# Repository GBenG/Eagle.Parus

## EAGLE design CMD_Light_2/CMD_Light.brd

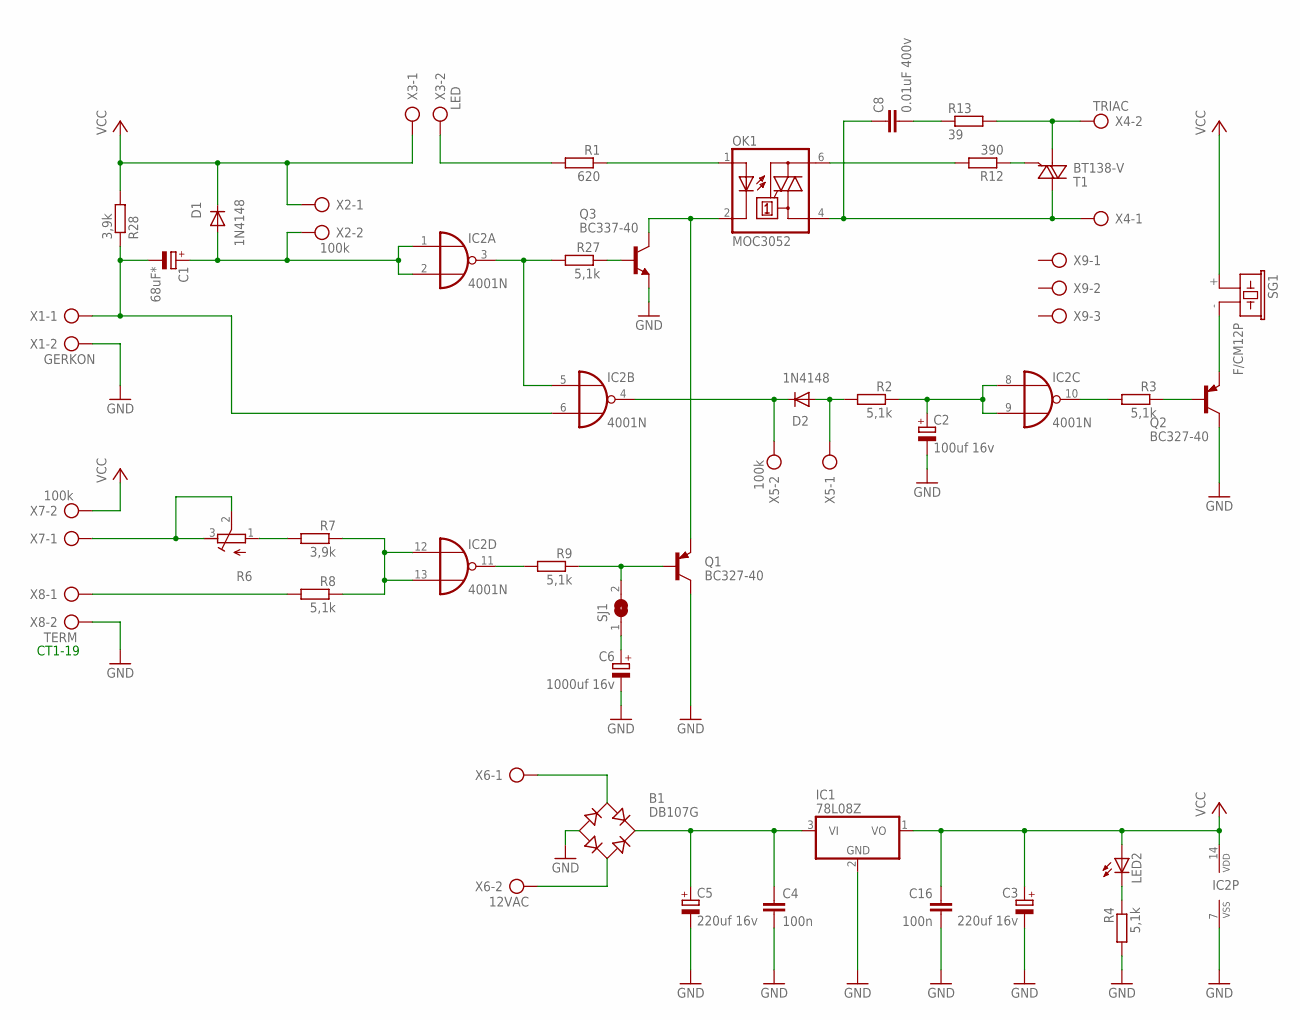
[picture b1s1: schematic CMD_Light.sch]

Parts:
B1: DB107G; DB
C1: 68uF*; E3,5-8
C2: 100uf 16v; E3,5-8
C3, C5: 220uf 16v; E3,5-8
C4, C16: 100n; C050-035X075
C6: 1000uf 16v; E5-10,5
C8: 0.01uF 400v; C075-063X106
D1: 1N4148; DO41-8
D2: 1N4148; DO41-10
IC1: 78L08Z; TO92
IC2: 4001N; DIL14
LED2: LED3MM
OK1: MOC3052; DIL06
Q1, Q2: BC327-40; TO92-EBC
Q3: BC337-40; TO92-EBC
R1: 620; 0207/10
R2, R3, R4, R8, R9, R27: 5,1k; 0207/10
R6: R-TRIMM3339P; RTRIM3339P
R7: 3,9k; 0207/10
R12: 390; 0207/10
R13: 39; 0411/12
R28: 3,9k; 0207/12
SG1: F/CM12P
SJ1: SJ
T1: BT138-V; TO220BV
X1: GERKON; AK500/2
X2, X5, X7: 100k; AK500/2
X3: LED; AK500/2
X4: TRIAC; AK500/2
X6: 12VAC; AK500/2
X8: TERM; AK500/2
X9: AK500/3

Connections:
GND: B1.-, C2.-, C3.-, C4.2, C5.-, C6.-, C16.2, IC1.2 (GND), IC2.7 (VSS), Q1.C, Q2.C, Q3.E, R4.2, X1.2, X8.2
unnamed: Q3.B, R27.1
unnamed: IC2.3 (O), IC2.5 (I0), R27.2
unnamed: C1.-, IC2.6 (I1), R28.1, X1.1
unnamed: OK1.1 (A), R1.1
unnamed: OK1.2 (C), Q1.E, Q3.C
unnamed: C6.+, SJ1.1
unnamed: R12.1, T1.G
unnamed: R1.2, X3.2
unnamed: B1.AC2, X6.2
unnamed: C2.+, IC2.8 (I0), IC2.9 (I1), R2.1
unnamed: IC2.10 (O), R3.2
unnamed: Q2.B, R3.1
unnamed: R13.2, T1.T1 (A1), X4.2
unnamed: Q2.E, SG1.- (2)
unnamed: B1.+, C4.1, C5.+, IC1.3 (VI)
unnamed: D2.A, R2.2, X5.1
unnamed: C8.2, R13.1
unnamed: C1.+, D1.A, IC2.1 (I0), IC2.2 (I1), X2.2
unnamed: IC2.12 (I0), IC2.13 (I1), R7.1, R8.1
unnamed: LED2.K (C), R4.1
unnamed: R6.2 (S), R6.3 (E), X7.1
unnamed: IC2.11 (O), R9.2
unnamed: R6.1 (A), R7.2
unnamed: R8.2, X8.1
unnamed: D2.C, IC2.4 (O), X5.2
unnamed: B1.AC1, X6.1
unnamed: OK1.6 (A2), R12.2
unnamed: Q1.B, R9.1, SJ1.2
unnamed: C8.1, OK1.4 (A1), T1.T2 (A2), X4.1
VCC: C3.+, C16.1, D1.C, IC1.1 (VO), IC2.14 (VDD), LED2.A, R28.2, SG1.+ (1), X2.1, X3.1, X7.2

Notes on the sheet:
CT1-19

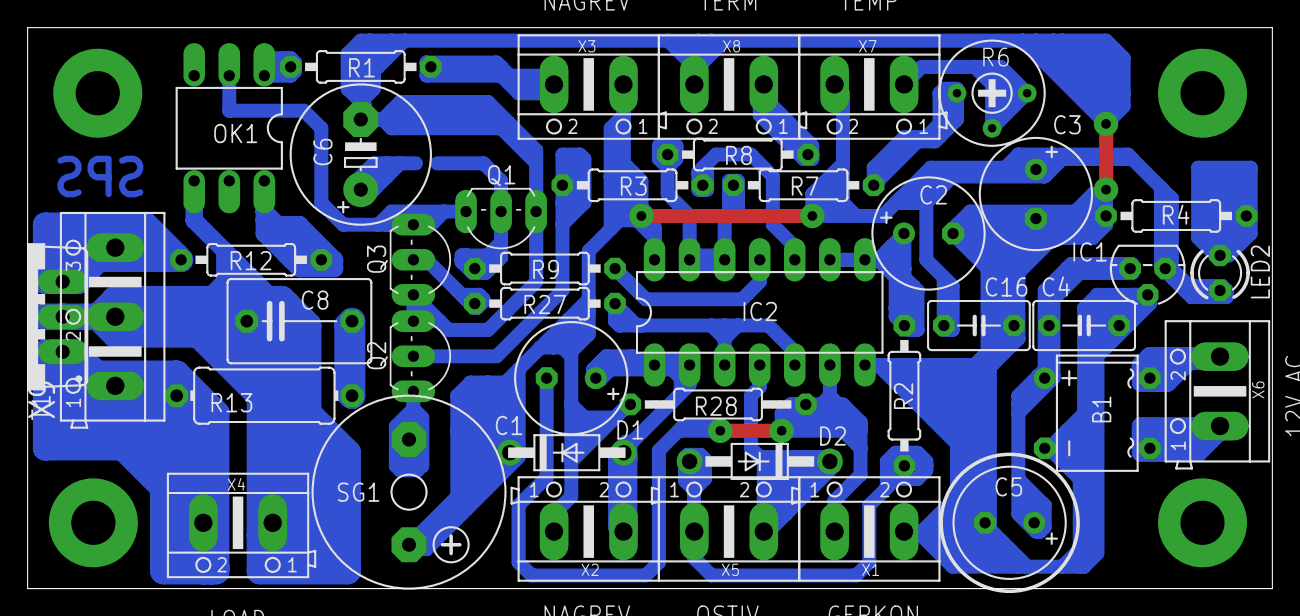
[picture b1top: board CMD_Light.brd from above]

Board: 2 copper layers, 90.2 x 40.6 mm, 42 parts (1 on the bottom side), 31 nets.

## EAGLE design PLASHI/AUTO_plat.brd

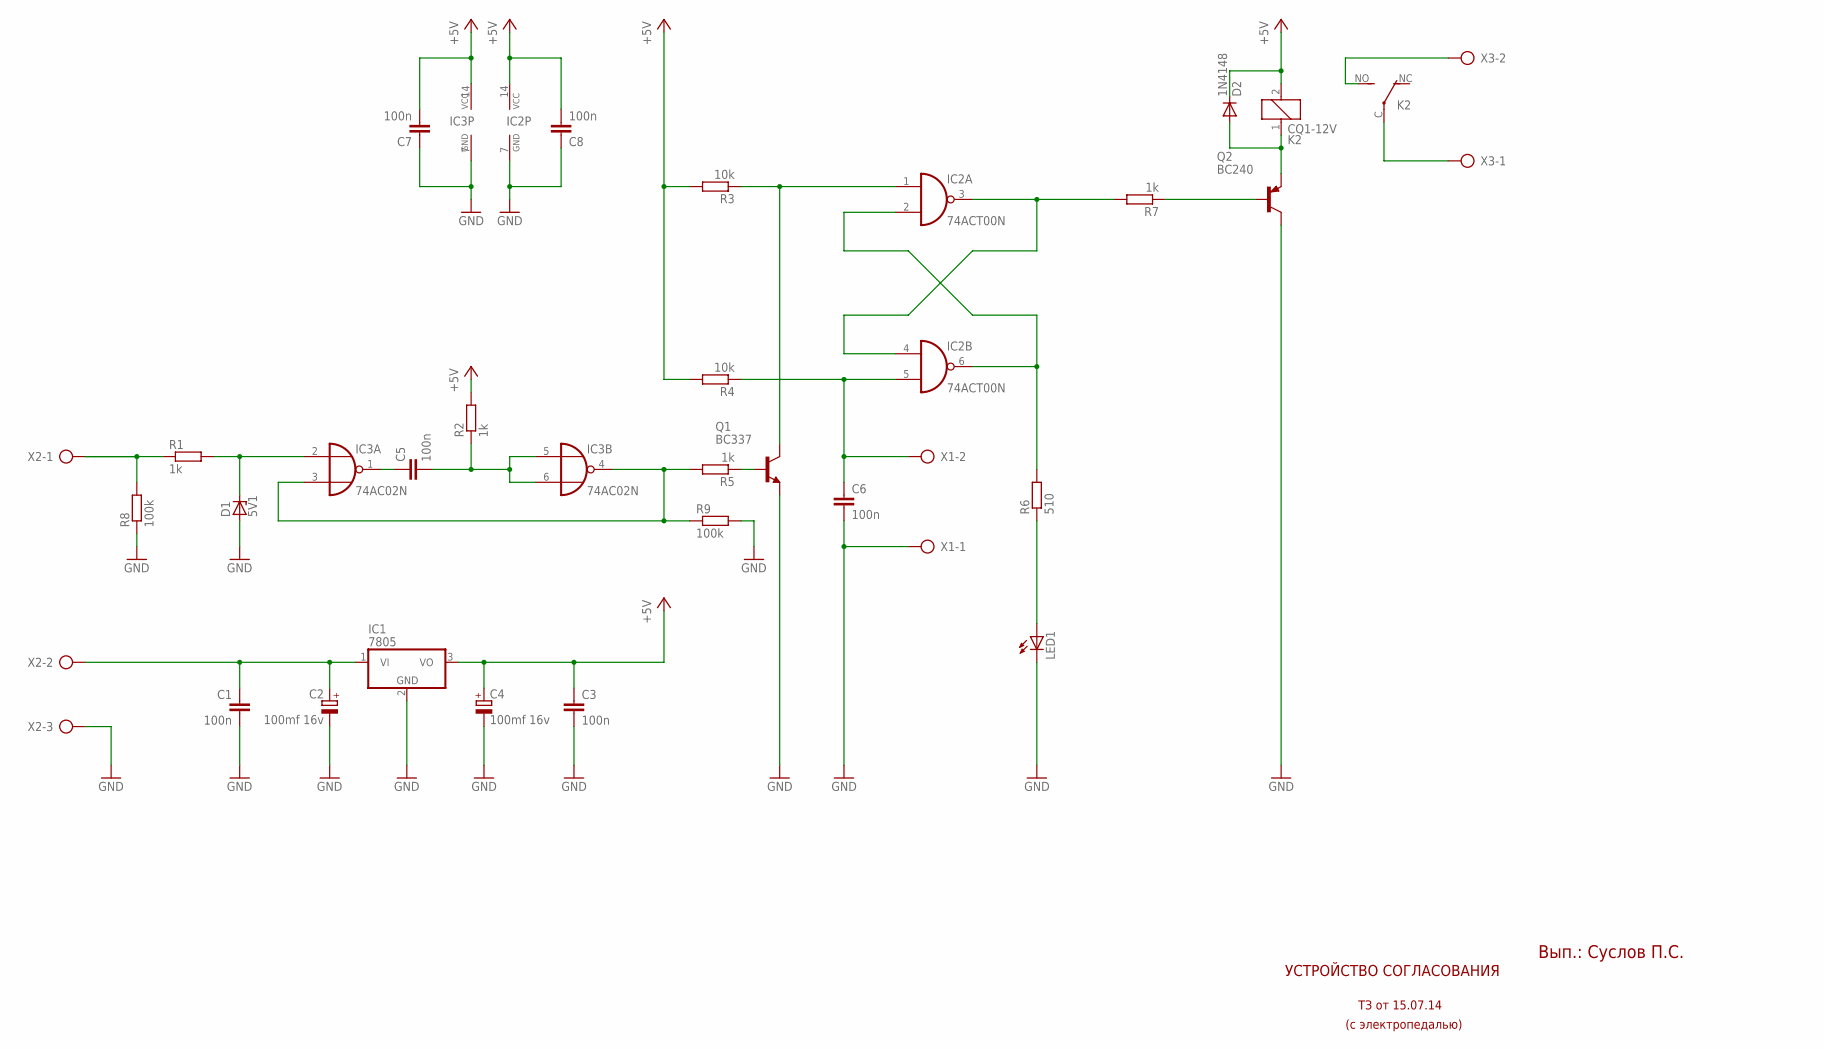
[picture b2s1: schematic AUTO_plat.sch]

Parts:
C1, C3, C5, C6, C7, C8: 100n; C025-030X050
C2, C4: 100mf 16v; E3,5-8
D1: 5V1; DO41Z10
D2: 1N4148; DO35-10
IC1: 7805; TO220V
IC2: 74ACT00N; DIL14
IC3: 74AC02N; DIL14
K2: CQ1-12V; CQ1
LED1: LED3MM
Q1: BC337; TO92
Q2: BC240; TO220
R1, R2, R5, R7: 1k; 0207/10
R3, R4: 10k; 0207/10
R6: 510; 0207/10
R8, R9: 100k; 0207/10
X1, X3: AK500/2
X2: AK500/3

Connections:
+5V: C3.1, C4.+, C7.2, C8.2, D2.C, IC1.3 (VO), IC2.14 (VCC), IC3.14 (VCC), K2.2, R2.2, R3.2, R4.2
GND: C1.2, C2.-, C3.2, C4.-, C6.2, C7.1, C8.1, D1.A, IC1.2 (GND), IC2.7 (GND), IC3.7 (GND), LED1.K (C), Q1.1 (E), Q2.2 (C), R8.1, R9.2, X1.1, X2.3
unnamed: C1.1, C2.+, IC1.1 (VI), X2.2
unnamed: R1.1, R8.2, X2.1
unnamed: D1.C, IC3.2 (I0), R1.2
unnamed: C5.1, IC3.1 (O)
unnamed: C5.2, IC3.5 (I0), IC3.6 (I1), R2.1
unnamed: IC3.3 (I1), IC3.4 (O), R5.2, R9.1
unnamed: IC2.3 (O), IC2.4 (I0), R7.2
unnamed: IC2.2 (I1), IC2.6 (O), R6.2
unnamed: IC2.1 (I0), Q1.3 (C), R3.1
unnamed: C6.1, IC2.5 (I1), R4.1, X1.2
unnamed: Q1.2 (B), R5.1
unnamed: LED1.A, R6.1
unnamed: Q2.1 (B), R7.1
unnamed: D2.A, K2.1, Q2.3 (E)
unnamed: K2.C, X3.1
unnamed: K2.NO (S), X3.2

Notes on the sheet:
УСТРОЙСТВО СОГЛАСОВАНИЯ
ТЗ от 15.07.14
(с электропедалью)
Вып.: Суслов П.С.

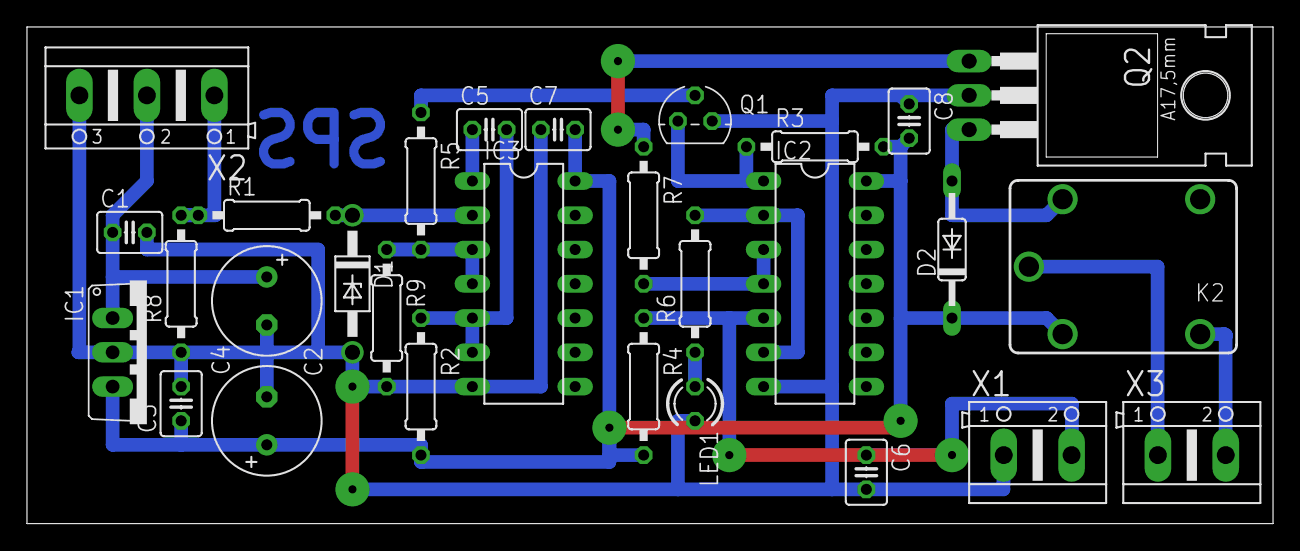
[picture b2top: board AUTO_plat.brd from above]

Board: 2 copper layers, 92.4 x 36.8 mm, 29 parts (0 on the bottom side), 18 nets.

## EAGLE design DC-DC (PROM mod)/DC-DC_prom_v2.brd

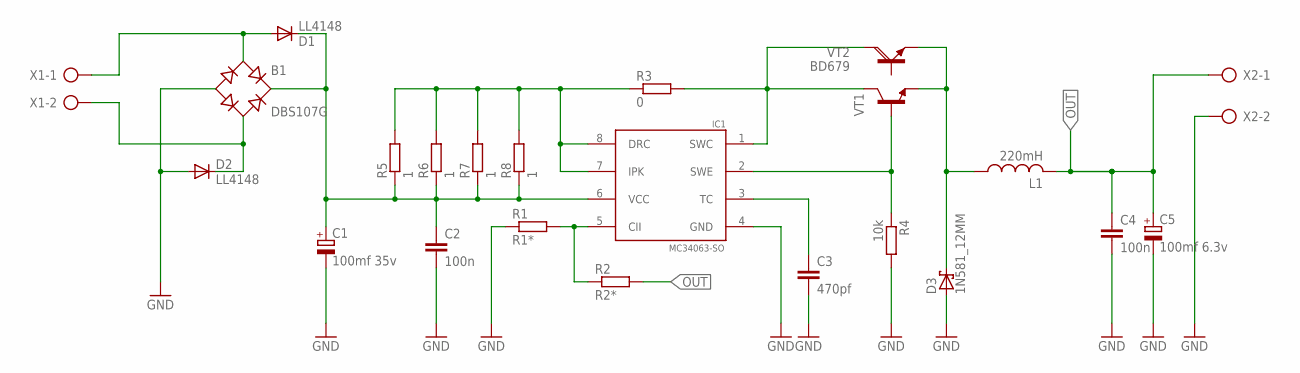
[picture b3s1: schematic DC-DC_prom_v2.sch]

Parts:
B1: DBS107G; DBS
C1: 100mf 35v; E2,5-7
C2, C4: 100n; C0805
C3: 470pf; C0805
C5: 100mf 6.3v; E2,5-7
D1, D2: LL4148; SOD80_DO213AA_MINIMELF
D3: 1N581_12MM; DO41-12
IC1: MC34063-SO; SO8
L1: 220mH; 6000-XXXX-RC
R1: R1*; M0805
R2: R2*; M0805
R3: 0; M1406
R4: 10k; M0805
R5, R6, R7, R8: 1; M1206
VT1: BCX56-16; SOT89
VT2: BD679; TO126AV
X1, X2: AK500/2

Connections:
GND: B1.-, C1.-, C2.2, C3.2, C4.2, C5.-, D2.A, D3.A, IC1.4 (GND), R1.1, R4.2, X2.2
unnamed: D3.C, L1.1, VT1.E, VT2.E
unnamed: IC1.5 (CII), R1.2, R2.1
unnamed: IC1.1 (SWC), R3.2, VT1.C, VT2.C
unnamed: IC1.7 (IPK), IC1.8 (DRC), R3.1, R5.2, R6.2, R7.2, R8.2
unnamed: B1.AC1, D1.A, X1.1
unnamed: B1.AC2, D2.C, X1.2
unnamed: B1.+, C1.+, C2.1, D1.C, IC1.6 (VCC), R5.1, R6.1, R7.1, R8.1
unnamed: C3.1, IC1.3 (TC)
unnamed: IC1.2 (SWE), R4.1, VT1.B
OUT: C4.1, C5.+, L1.2, R2.2, X2.1

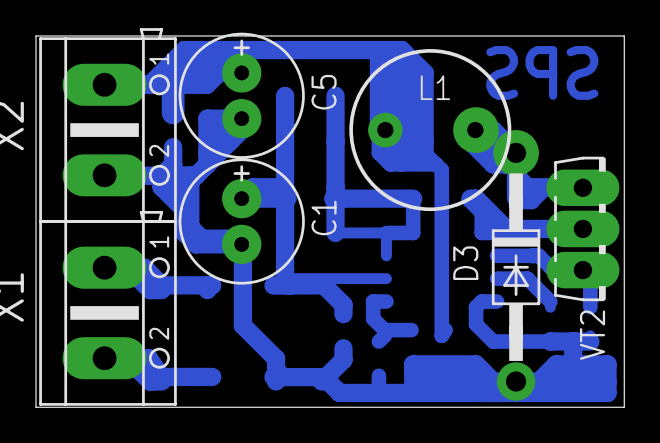
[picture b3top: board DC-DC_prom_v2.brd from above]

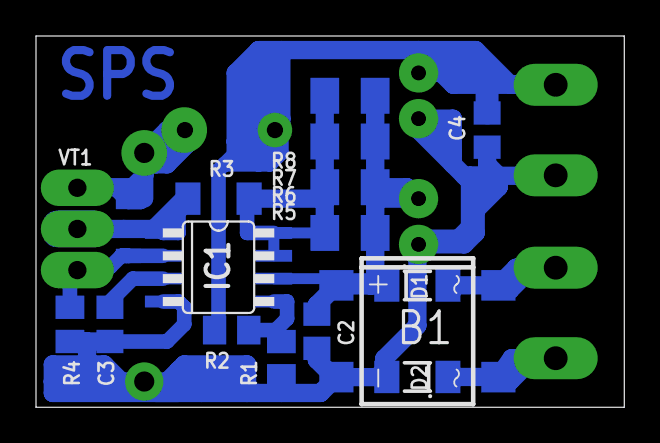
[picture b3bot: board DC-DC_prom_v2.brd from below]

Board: 2 copper layers, 32.7 x 20.6 mm, 23 parts (16 on the bottom side), 11 nets.

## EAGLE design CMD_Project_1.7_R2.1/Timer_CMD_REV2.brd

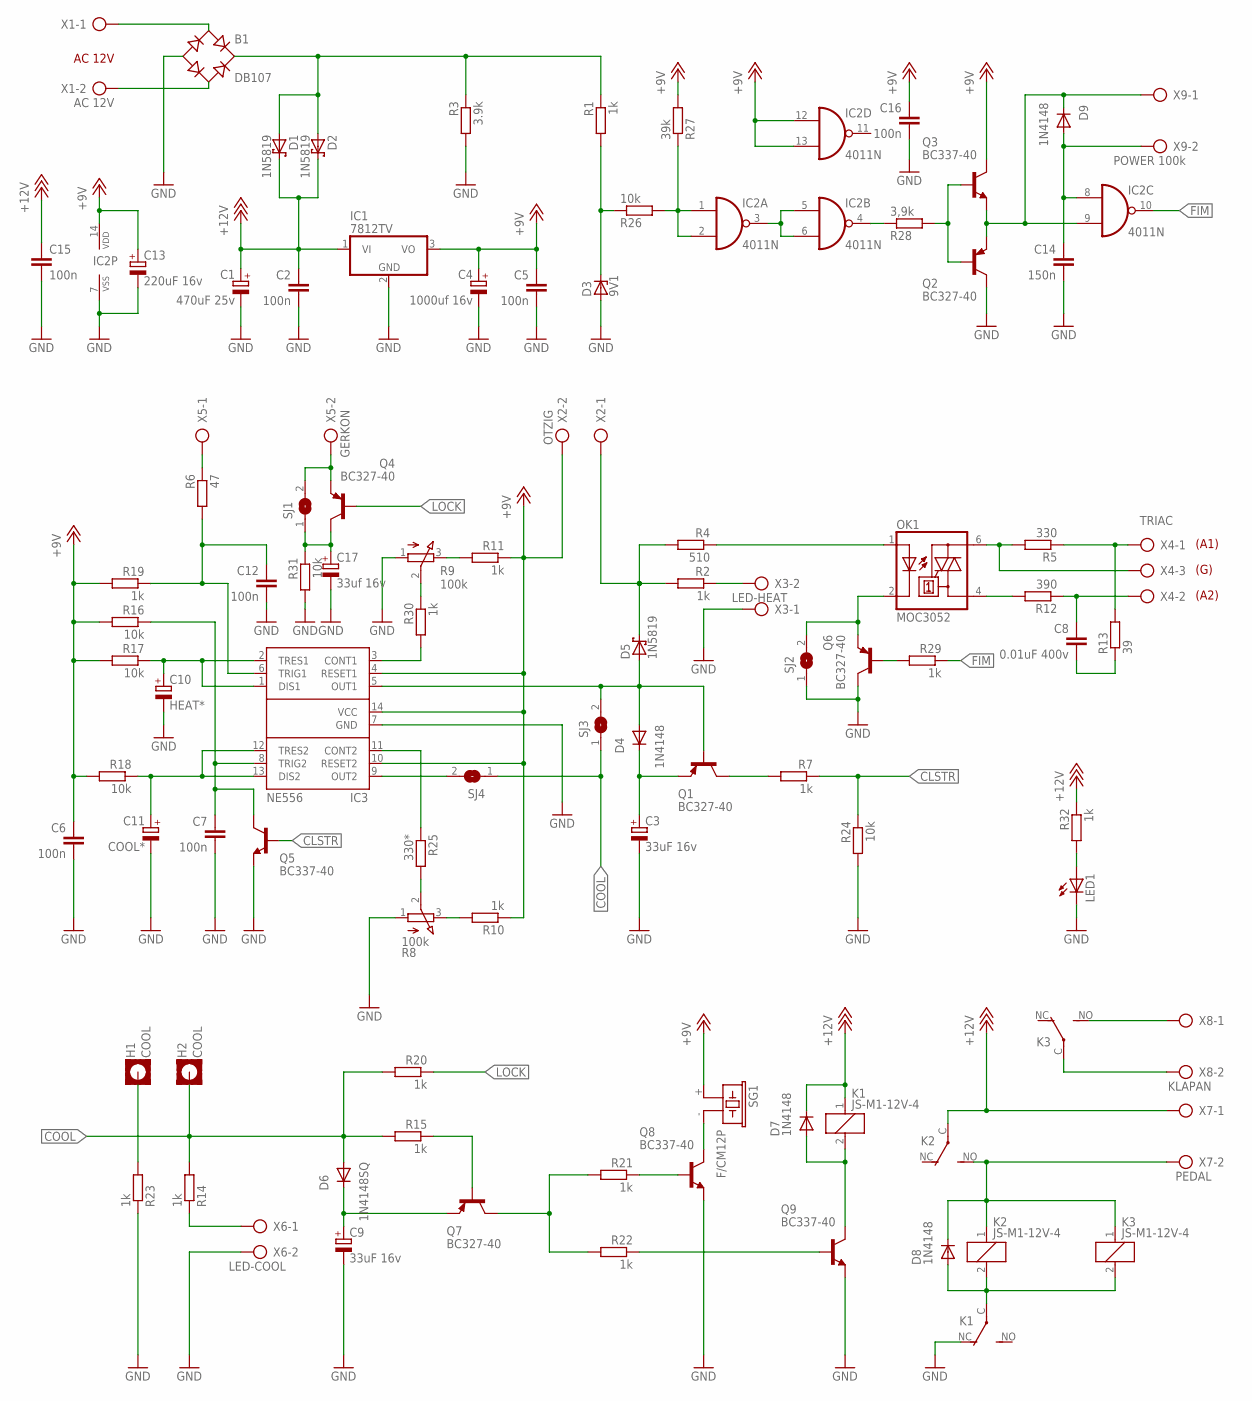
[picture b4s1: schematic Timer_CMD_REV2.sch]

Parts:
B1: DB107; DB
C1: 470uF 25v; E3,5-8
C2, C5, C15, C16: 100n; C050-035X075
C3, C9: 33uF 16v; E3,5-8
C4: 1000uf 16v; E5-10,5
C6, C7, C12: 100n; C025-030X050
C8: 0.01uF 400v; C075-063X106
C10: HEAT*; E3,5-10
C11: COOL*; E3,5-10
C13: 220uF 16v; E3,5-8
C14: 150n; C050-035X075
C17: 33uf 16v; E2,5-6
D1, D2, D5: 1N5819; DO41-7.6
D3: 9V1; DO41Z12
D4, D7, D8, D9: 1N4148; DO35-7SQ
D6: 1N4148SQ; DO35-10_SQ
H1, H2: COOL; 4MM-PAD-SQUARE
IC1: 7812TV; TO220V
IC2: 4011N; DIL14
IC3: NE556; DIL14
K1, K2, K3: JS-M1-12V-4; JS-M
LED1: LED3MM
OK1: MOC3052; DIL06
Q1, Q2, Q4, Q6, Q7: BC327-40; TO92-EBC
Q3, Q5, Q8, Q9: BC337-40; TO92-EBC
R1, R2, R7, R10, R11, R14, R15, R19, R20, R21, R22, R23, R29, R32: 1k; 0207/10
R3: 3.9k; 0207/10
R4: 510; 0207/10
R5: 330; 0207/10
R6: 47; 0207/10
R8, R9: 100k; 3RP/1610N
R12: 390; 0207/10
R13: 39; 0411/12
R16, R17, R18, R24, R26, R31: 10k; 0207/10
R25: 330*; 0207/10
R27: 39k; 0207/10
R28: 3,9k; 0207/10
R30: 1k; 0207/11
SG1: F/CM12P
SJ1, SJ2, SJ3, SJ4: SJ
X1: AC 12V; AK500/2
X2: OTZIG; AK500/2
X3: LED-HEAT; AK500/2
X4: TRIAC; AK500/3
X5: GERKON; AK500/2
X6: LED-COOL; AK500/2
X7: PEDAL; AK500/2
X8: KLAPAN; AK500/2
X9: POWER 100k; AK500/2

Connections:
788: Q1.C, R7.2
+9V: C4.+, C5.1, C6.1, C13.+, C16.1, IC1.3 (VO), IC2.12 (I0), IC2.13 (I1), IC2.14 (VDD), IC3.4 (RESET1), IC3.10 (RESET2), IC3.14 (VCC), Q3.C, R10.1, R11.1, R16.2, R17.2, R18.2, R19.2, R27.2, SG1.+ (1), X2.2
+12V: C1.+, C2.1, C15.1, D1.C, D2.C, D7.C, IC1.1 (VI), K1.1, K2.C, R32.1, X7.1
CLSTR: Q5.B, R7.1, R24.1
COOL: D6.A, H2.B2,8, R14.2, R15.2, R20.2, SJ3.1, SJ4.1
FIM: IC2.10 (O), R29.1
GND: B1.-, C1.-, C2.2, C3.-, C4.-, C5.2, C6.2, C7.2, C9.-, C10.-, C11.-, C12.2, C13.-, C14.2, C15.2, C16.2, C17.-, D3.A, IC1.2 (GND), IC2.7 (VSS), IC3.7 (GND), K1.NC (O), LED1.K (C), Q2.C, Q5.E, Q6.C, Q8.E, Q9.E, R3.2, R8.1 (A), R9.1 (A), R23.1, R24.2, R31.2, SJ2.1, X3.1, X6.2
LOCK: Q4.B, R20.1
unnamed: B1.+, D1.A, D2.A, R1.1, R3.1
unnamed: R6.1, X5.1
unnamed: R2.1, X3.2
unnamed: OK1.4 (A1), R12.2
unnamed: D3.C, R1.2, R26.1
unnamed: D5.C, R2.2, R4.2, X2.1
unnamed: C8.1, R12.1, X4.2
unnamed: C10.+, IC3.1 (DIS1), IC3.2 (TRES1), R17.1
unnamed: B1.AC2, X1.2
unnamed: B1.AC1, X1.1
unnamed: D4.A, D5.A, IC3.5 (OUT1), Q1.B, SJ3.2
unnamed: OK1.2 (C), Q6.E, SJ2.2
unnamed: R5.1, R13.2, X4.1
unnamed: C8.2, R13.1
unnamed: Q7.B, R15.1
unnamed: Q7.C, R21.2, R22.2
unnamed: D7.A, K1.2, Q9.C
unnamed: Q8.B, R21.1
unnamed: C11.+, IC3.12 (TRES2), IC3.13 (DIS2), R18.1
unnamed: C12.1, IC3.6 (TRIG1), R6.2, R19.1
unnamed: R9.3 (E), R11.2
unnamed: IC3.11 (CONT2), R25.1
unnamed: Q4.E, SJ1.2, X5.2
unnamed: R8.3 (E), R10.2
unnamed: IC2.1 (I0), IC2.2 (I1), R26.2, R27.1
unnamed: Q9.B, R22.1
unnamed: D8.C, K2.1, K2.NO (S), K3.1, X7.2
unnamed: Q8.C, SG1.- (2)
unnamed: OK1.6 (A2), R5.2, X4.3
unnamed: C3.+, D4.C, Q1.E
unnamed: D8.A, K1.C, K2.2, K3.2
unnamed: K3.NO (S), X8.1
unnamed: R14.1, X6.1
unnamed: H1.B2,8, R23.2
unnamed: IC3.3 (CONT1), R30.2
unnamed: IC3.9 (OUT2), SJ4.2
unnamed: IC2.4 (O), R28.1
unnamed: IC2.3 (O), IC2.5 (I0), IC2.6 (I1)
unnamed: OK1.1 (A), R4.1
unnamed: C7.1, IC3.8 (TRIG2), Q5.C, R16.1
unnamed: Q2.B, Q3.B, R28.2
unnamed: K3.C, X8.2
unnamed: C14.1, D9.A, IC2.8 (I0), X9.2
unnamed: Q6.B, R29.2
unnamed: R8.2 (S), R25.2
unnamed: D9.C, IC2.9 (I1), Q2.E, Q3.E, X9.1
unnamed: C17.+, Q4.C, R31.1, SJ1.1
unnamed: C9.+, D6.C, Q7.E
unnamed: R9.2 (S), R30.1
unnamed: LED1.A, R32.2

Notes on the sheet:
AC 12V
(A1)
(G)
(A2)

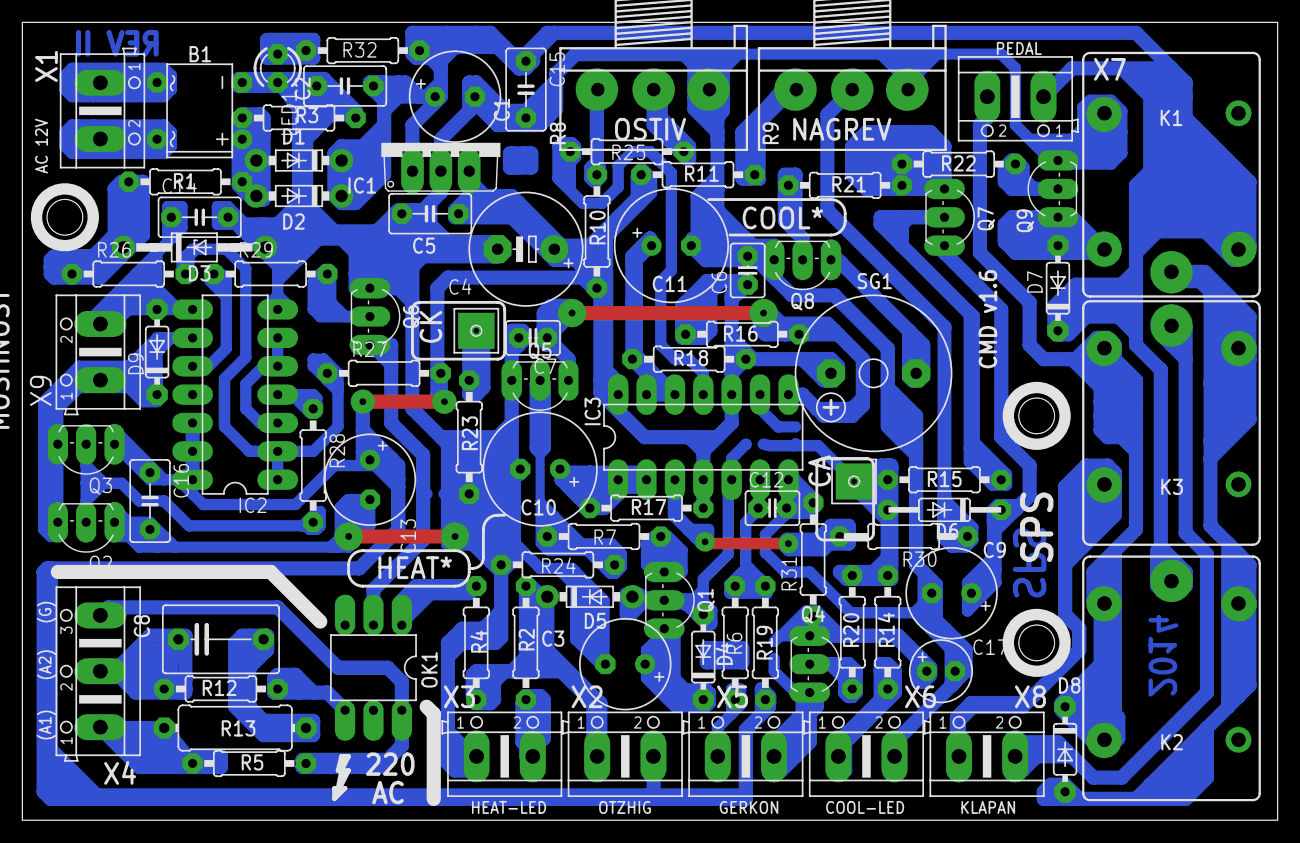
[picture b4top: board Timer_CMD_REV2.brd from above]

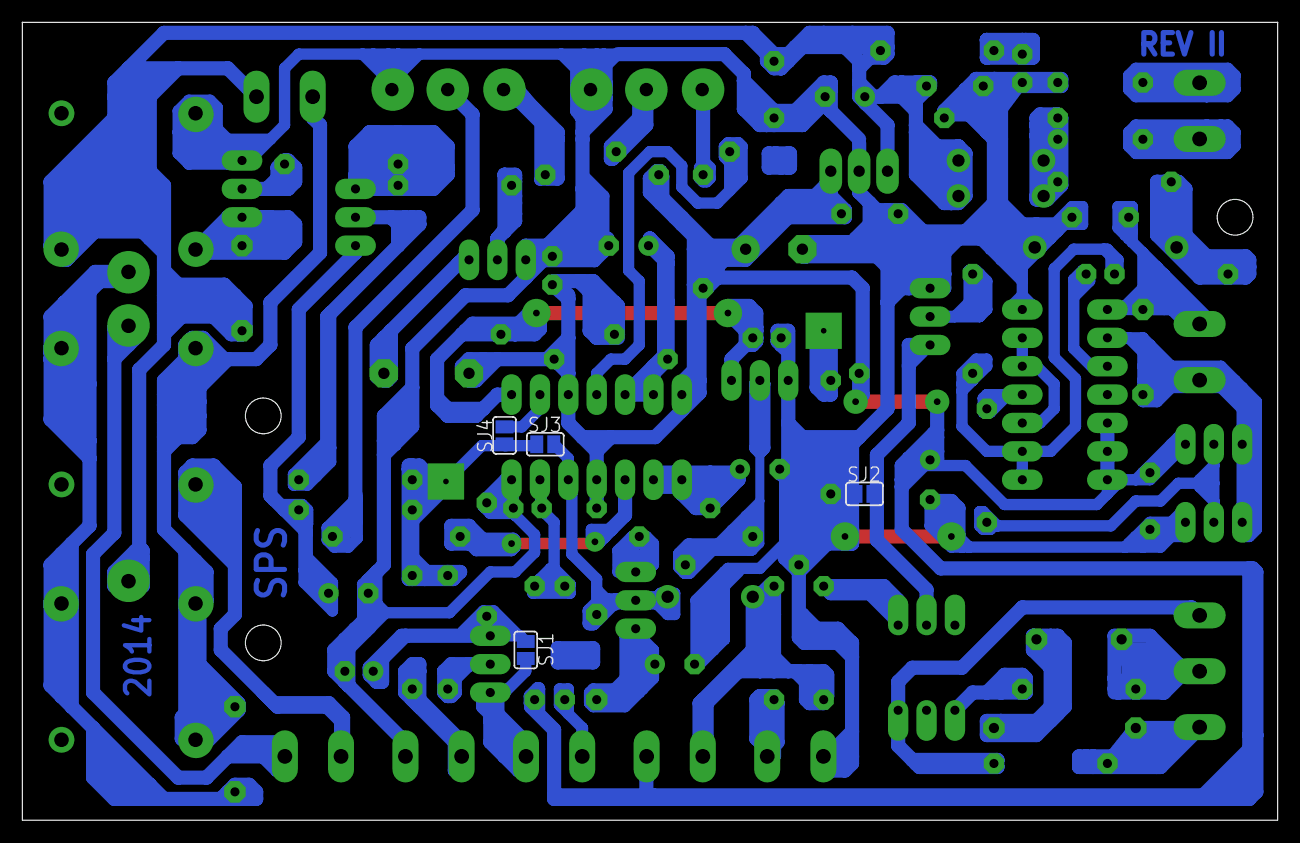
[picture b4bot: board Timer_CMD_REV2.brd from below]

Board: 2 copper layers, 112.4 x 71.4 mm, 93 parts (4 on the bottom side), 58 nets.

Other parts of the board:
DRILEGEND: DRILEGEND

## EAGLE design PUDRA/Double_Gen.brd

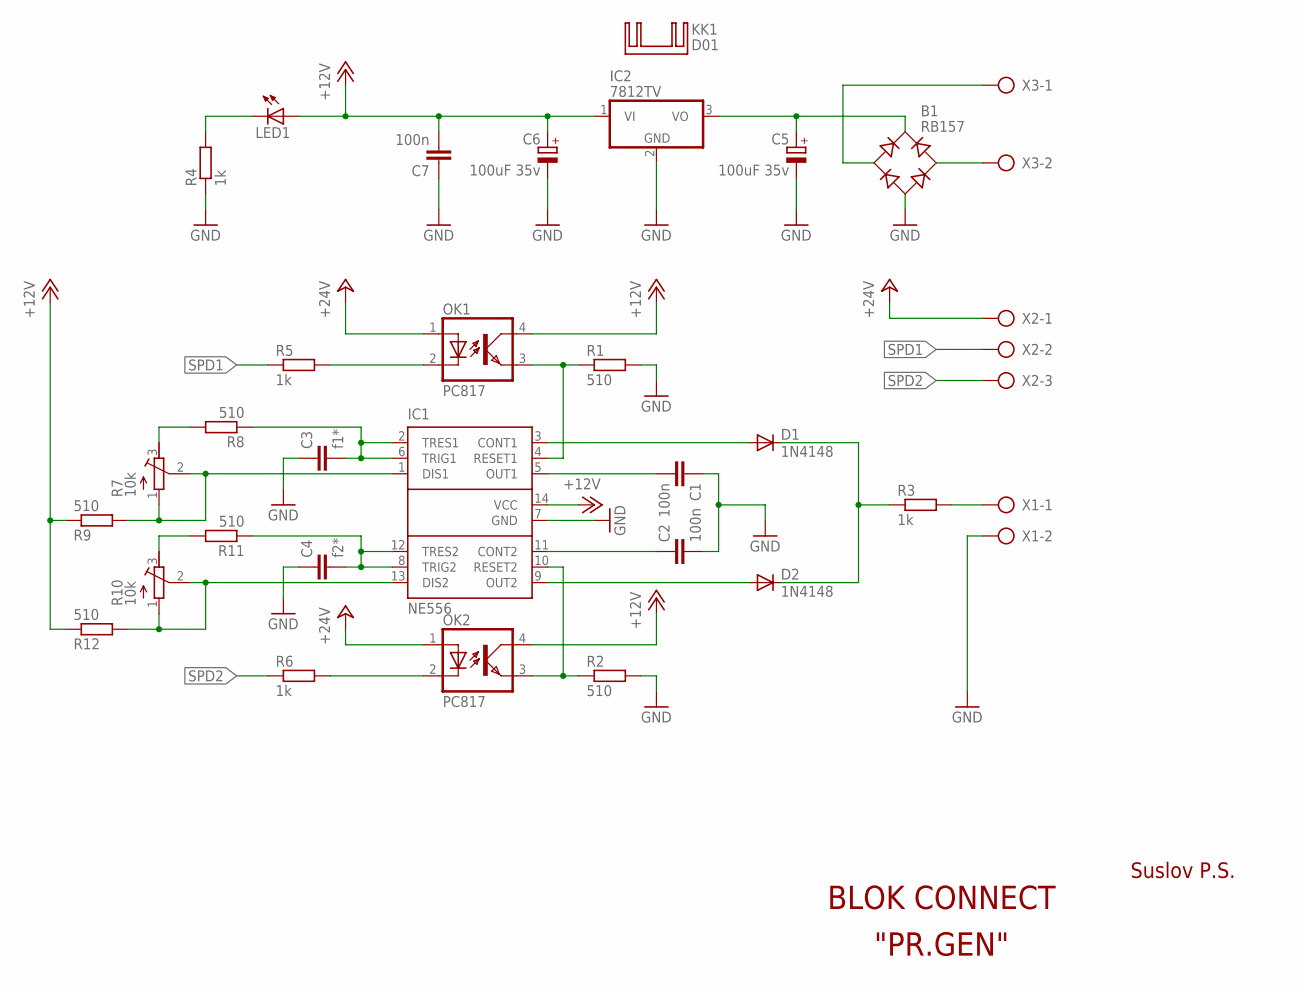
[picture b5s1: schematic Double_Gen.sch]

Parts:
B1: RB157; RB1A
C1, C2, C7: 100n; C050-050X075
C3: f1*; C050-050X075
C4: f2*; C050-050X075
C5, C6: 100uF 35v; E3,5-8
D1, D2: 1N4148; DO35-7
IC1: NE556; DIL14
IC2: 7812TV; TO220V
KK1: D01; D02S
LED1: LED5MM
OK1, OK2: PC817; DIL04
R1, R2, R8, R9, R11, R12: 510; 0207/10
R3, R4, R5, R6: 1k; 0207/10
R7, R10: 10k; RTRIM64W
X1, X3: AK500/2
X2: AK500/3

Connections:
+12V: C6.+, C7.1, IC1.14 (VCC), IC2.1 (VI), LED1.A, OK1.4 (COL), OK2.4 (COL), R9.1, R12.1
+24V: OK1.1 (A), OK2.1 (A), X2.1
GND: B1.-, C1.2, C2.2, C3.2, C4.2, C5.-, C6.-, C7.2, IC1.7 (GND), IC2.2 (GND), R1.2, R2.2, R4.1, X1.2
unnamed: C1.1, IC1.5 (OUT1)
unnamed: C2.1, IC1.11 (CONT2)
unnamed: IC1.4 (RESET1), OK1.3 (EMIT), R1.1
unnamed: IC1.10 (RESET2), OK2.3 (EMIT), R2.1
unnamed: D1.A, IC1.3 (CONT1)
unnamed: R3.2, X1.1
unnamed: D2.A, IC1.9 (OUT2)
unnamed: D1.C, D2.C, R3.1
unnamed: OK1.2 (C), R5.2
unnamed: OK2.2 (C), R6.2
unnamed: B1.AC2, X3.2
unnamed: R7.3 (E), R8.2
unnamed: C3.1, IC1.2 (TRES1), IC1.6 (TRIG1), R8.1
unnamed: IC1.1 (DIS1), R7.1 (A), R7.2 (S), R9.2
unnamed: B1.AC1, X3.1
unnamed: R10.3 (E), R11.2
unnamed: C4.1, IC1.8 (TRIG2), IC1.12 (TRES2), R11.1
unnamed: IC1.13 (DIS2), R10.1 (A), R10.2 (S), R12.2
unnamed: B1.+, C5.+, IC2.3 (VO)
unnamed: LED1.K (C), R4.2
SPD1: R5.1, X2.2
SPD2: R6.1, X2.3

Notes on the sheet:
BLOK CONNECT
Suslov P.S.
"PR.GEN"

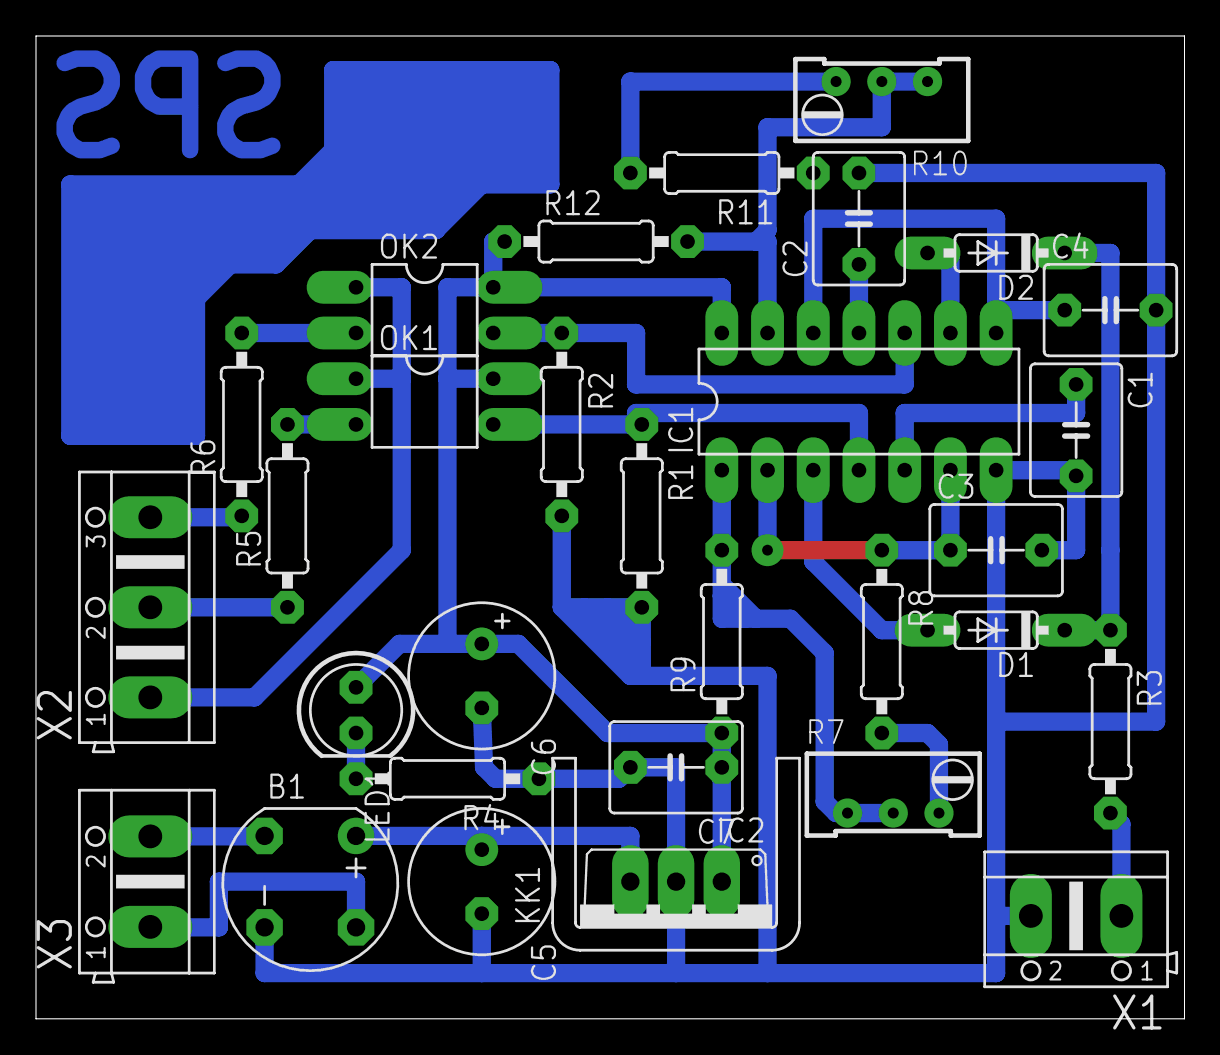
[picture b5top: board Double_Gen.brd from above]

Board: 2 copper layers, 63.8 x 54.6 mm, 31 parts (0 on the bottom side), 25 nets.

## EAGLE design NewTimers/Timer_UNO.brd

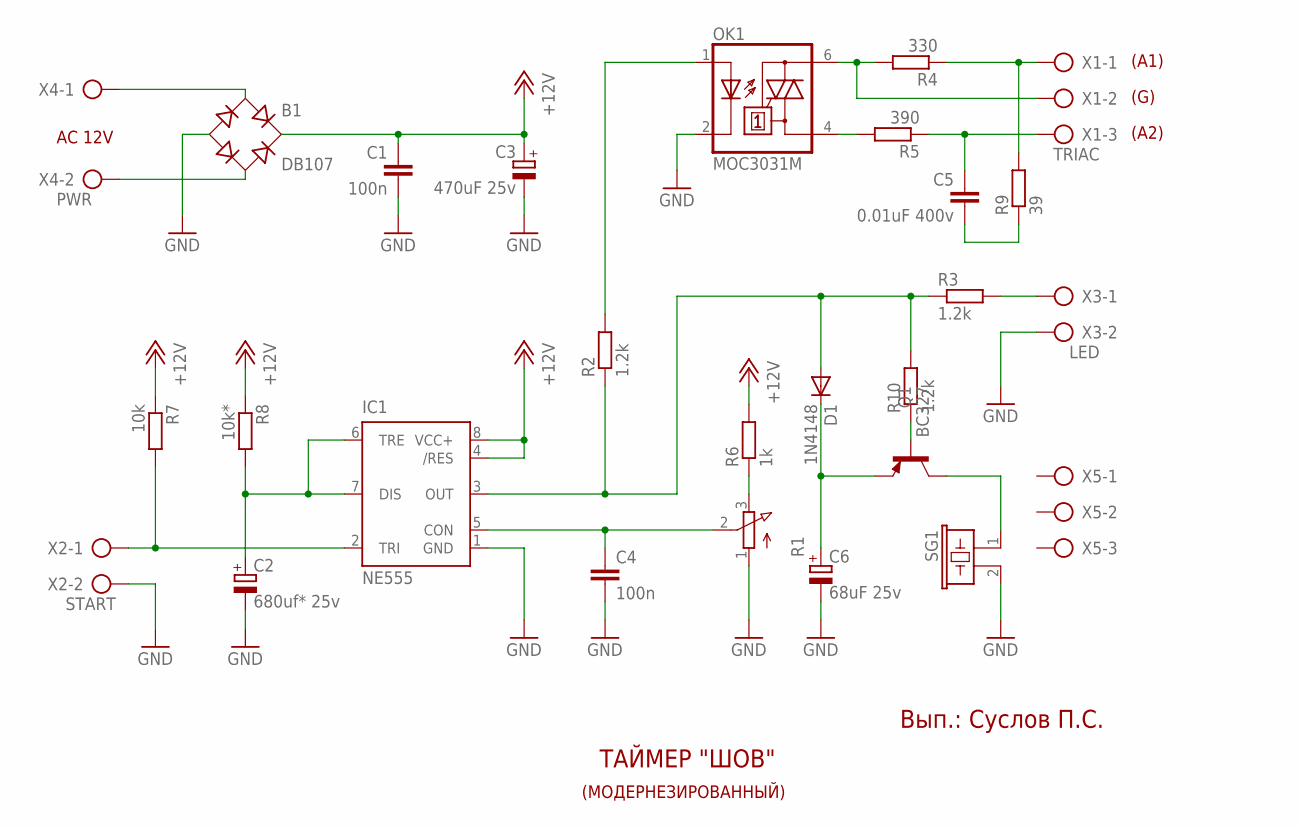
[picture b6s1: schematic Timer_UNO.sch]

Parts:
B1: DB107; DB
C1, C4: 100n; C025-030X050
C2: 680uf* 25v; E3,5-10
C3: 470uF 25v; E3,5-8
C5: 0.01uF 400v; C075-063X106
C6: 68uF 25v; E3,5-8
D1: 1N4148; DO35-7
IC1: NE555; DIL-08
OK1: MOC3031M; DIL06
Q1: BC327; TO92-EBC
R1: 3RP/1610N
R2, R3, R10: 1.2k; 0207/10
R4: 330; 0207/10
R5: 390; 0207/10
R6: 1k; 0207/10
R7: 10k; 0207/10
R8: 10k*; 0207/10
R9: 39; 0411/12
SG1: EFBAA40D101
X1: TRIAC; AK500/3
X2: START; AK500/2
X3: LED; AK500/2
X4: PWR; AK500/2
X5: AK500/3

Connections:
+12V: B1.+, C1.1, C3.+, IC1.4 (/RES), IC1.8 (VCC+), R6.2, R7.1, R8.1
GND: B1.-, C1.2, C2.-, C3.-, C4.2, C6.-, IC1.1 (GND), OK1.2 (C), R1.1 (A), SG1.2, X2.2, X3.2
unnamed: C4.1, IC1.5 (CON), R1.2 (S)
unnamed: D1.A, IC1.3 (OUT), R2.1, R3.1, R10.2
unnamed: R3.2, X3.1
unnamed: OK1.1 (A), R2.2
unnamed: C5.1, R5.1, X1.3
unnamed: OK1.4 (A1), R5.2
unnamed: OK1.6 (A2), R4.2, X1.2
unnamed: R4.1, R9.2, X1.1
unnamed: R1.3 (E), R6.1
unnamed: IC1.2 (TRI), R7.2, X2.1
unnamed: C2.+, IC1.6 (TRE), IC1.7 (DIS), R8.2
unnamed: B1.AC2, X4.2
unnamed: B1.AC1, X4.1
unnamed: C5.2, R9.1
unnamed: C6.+, D1.C, Q1.E
unnamed: Q1.B, R10.1
unnamed: Q1.C, SG1.1

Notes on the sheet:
(A1)
(G)
(A2)
AC 12V
ТАЙМЕР "ШОВ"
(МОДЕРНЕЗИРОВАННЫЙ)
Вып.: Суслов П.С.

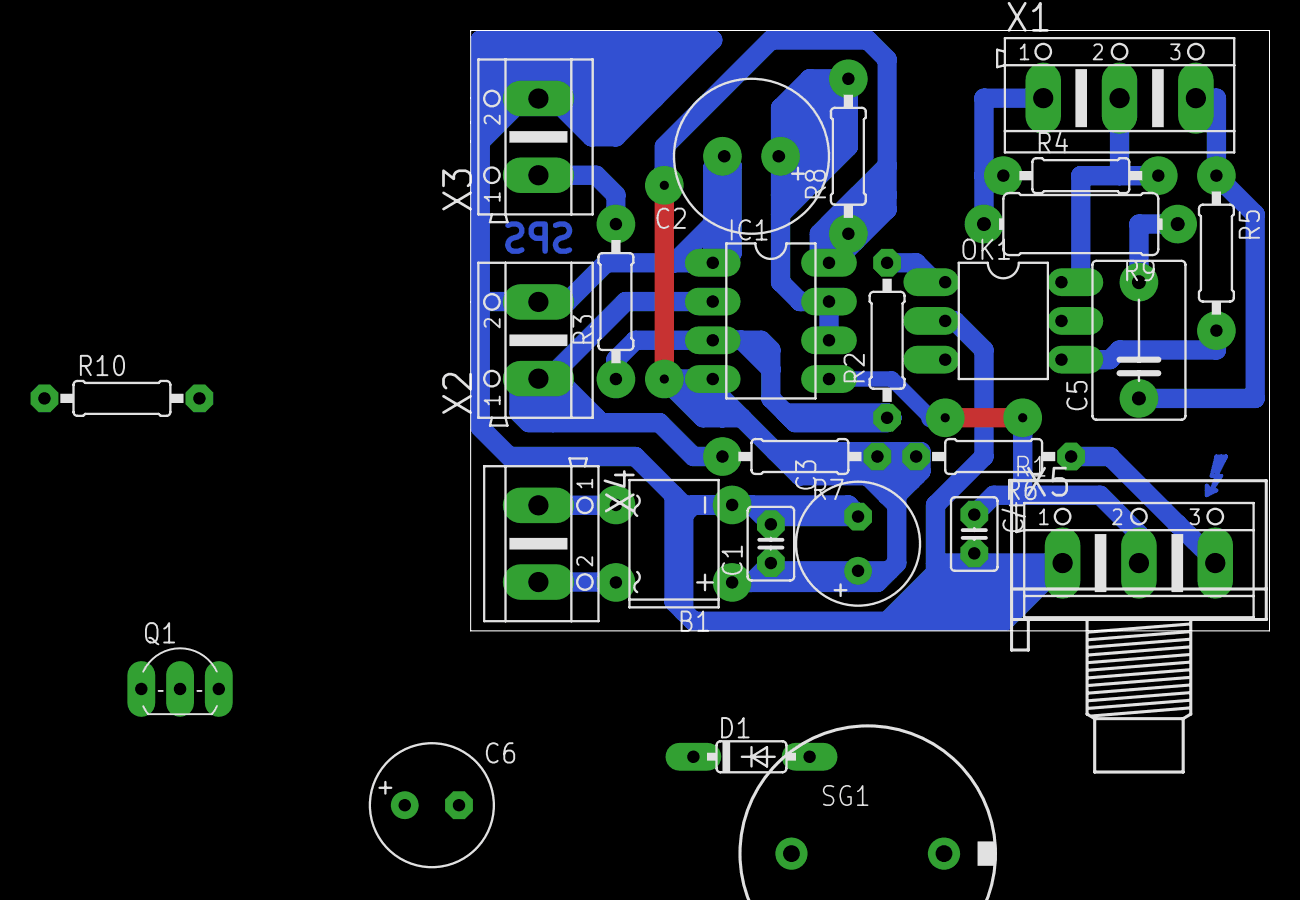
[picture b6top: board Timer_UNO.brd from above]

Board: 2 copper layers, 52.4 x 39.4 mm, 27 parts (0 on the bottom side), 19 nets.

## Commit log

2015-04-09 :tada: Added .gitattributes & .gitignore files
2015-04-09 Add files
    Все что есть на 09.04.2015
2015-04-14 Add ODESSA
    Добавлена схема дополнительного шкафа к установке "Одесса"
2015-05-18 ODESSA
    fix something
2015-06-19 Изменения на 19.06.2015
